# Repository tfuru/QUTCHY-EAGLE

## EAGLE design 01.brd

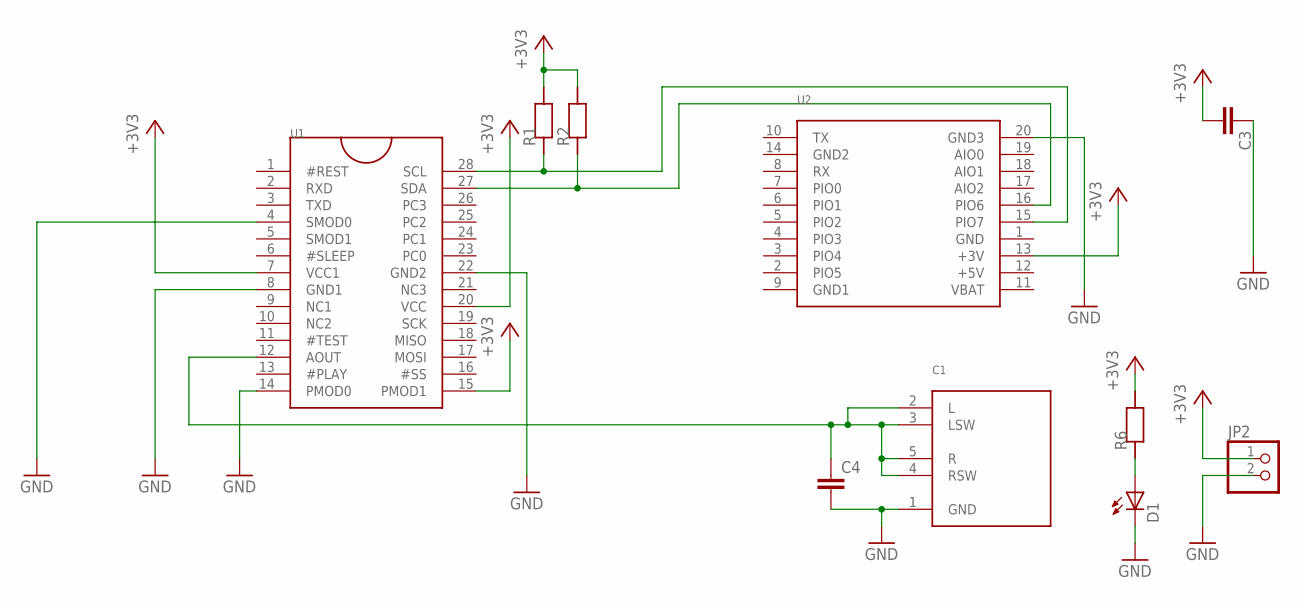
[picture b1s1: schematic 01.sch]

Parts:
C1: C-02384_AJ-1780; AJ-1780
C3, C4: C_1068; C0603
D1: LEDCHIPLED_0805; CHIPLED_0805
JP2: PINHD-1X2/90; 1X02/90
R1, R2, R6: R_1068; R0603
U1: I-06220_ATP3011F1-PU; DIL28-3
U2: KONASHI

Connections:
+3V3: C3.2, JP2.1, R1.2, R2.2, R6.2, U1.7 (VCC1), U1.15 (PMOD1), U1.20 (VCC), U2.13 (+3V)
GND: C1.1 (GND), C3.1, C4.2, D1.C, JP2.2, U1.4 (SMOD0), U1.8 (GND1), U1.14 (PMOD0), U1.22 (GND2), U2.20 (GND3)
unnamed: C1.2 (L), C1.3 (LSW), C1.4 (RSW), C1.5 (R), C4.1, U1.12 (AOUT)
unnamed: R2.1, U1.27 (SDA), U2.16 (PIO6)
unnamed: R1.1, U1.28 (SCL), U2.15 (PIO7)
unnamed: D1.A, R6.1

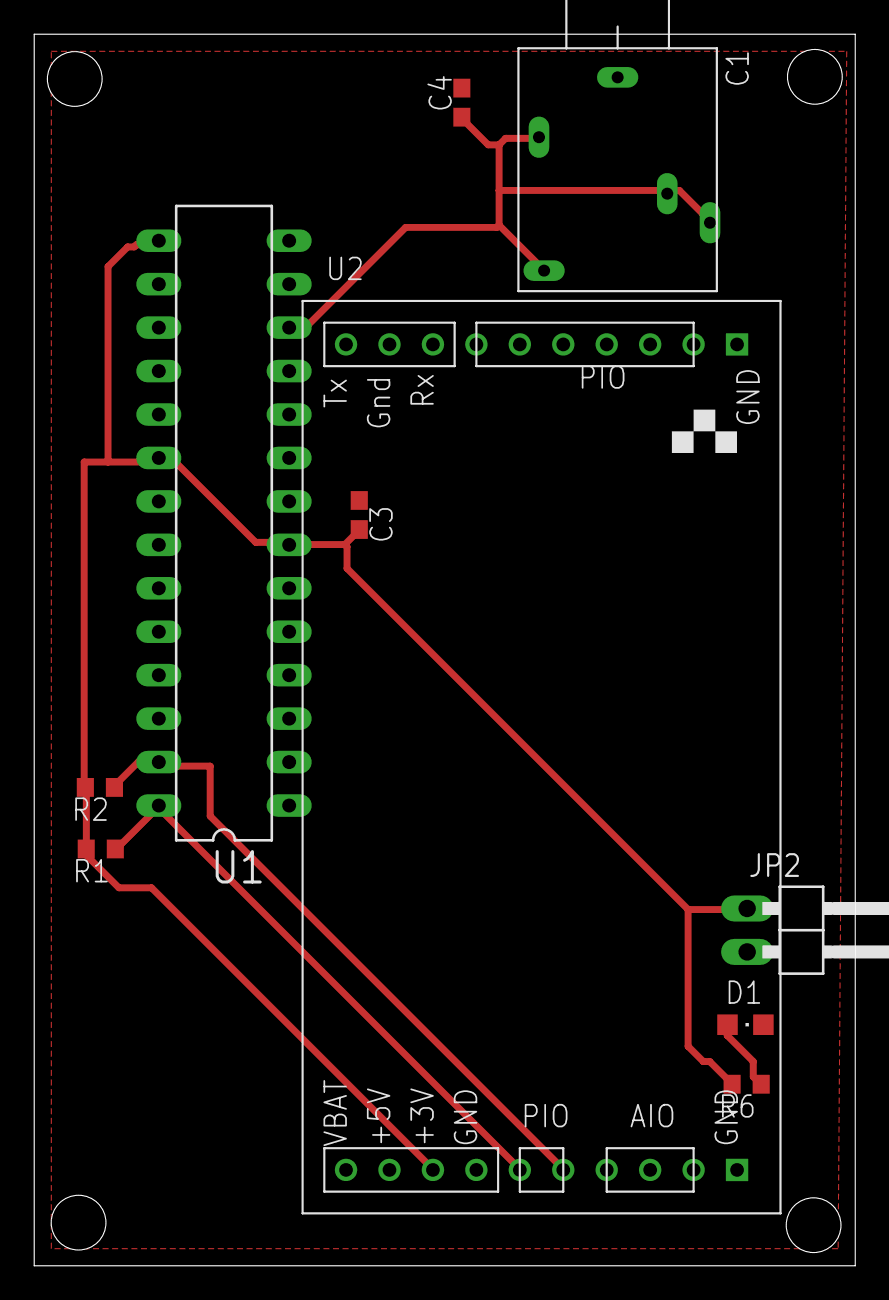
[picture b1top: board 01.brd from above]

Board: 2 copper layers, 48.0 x 72.0 mm, 10 parts (0 on the bottom side), 6 nets.

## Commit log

2014-02-26 add .gitignore
2014-02-26 GND 修正
2014-02-26 README修正
